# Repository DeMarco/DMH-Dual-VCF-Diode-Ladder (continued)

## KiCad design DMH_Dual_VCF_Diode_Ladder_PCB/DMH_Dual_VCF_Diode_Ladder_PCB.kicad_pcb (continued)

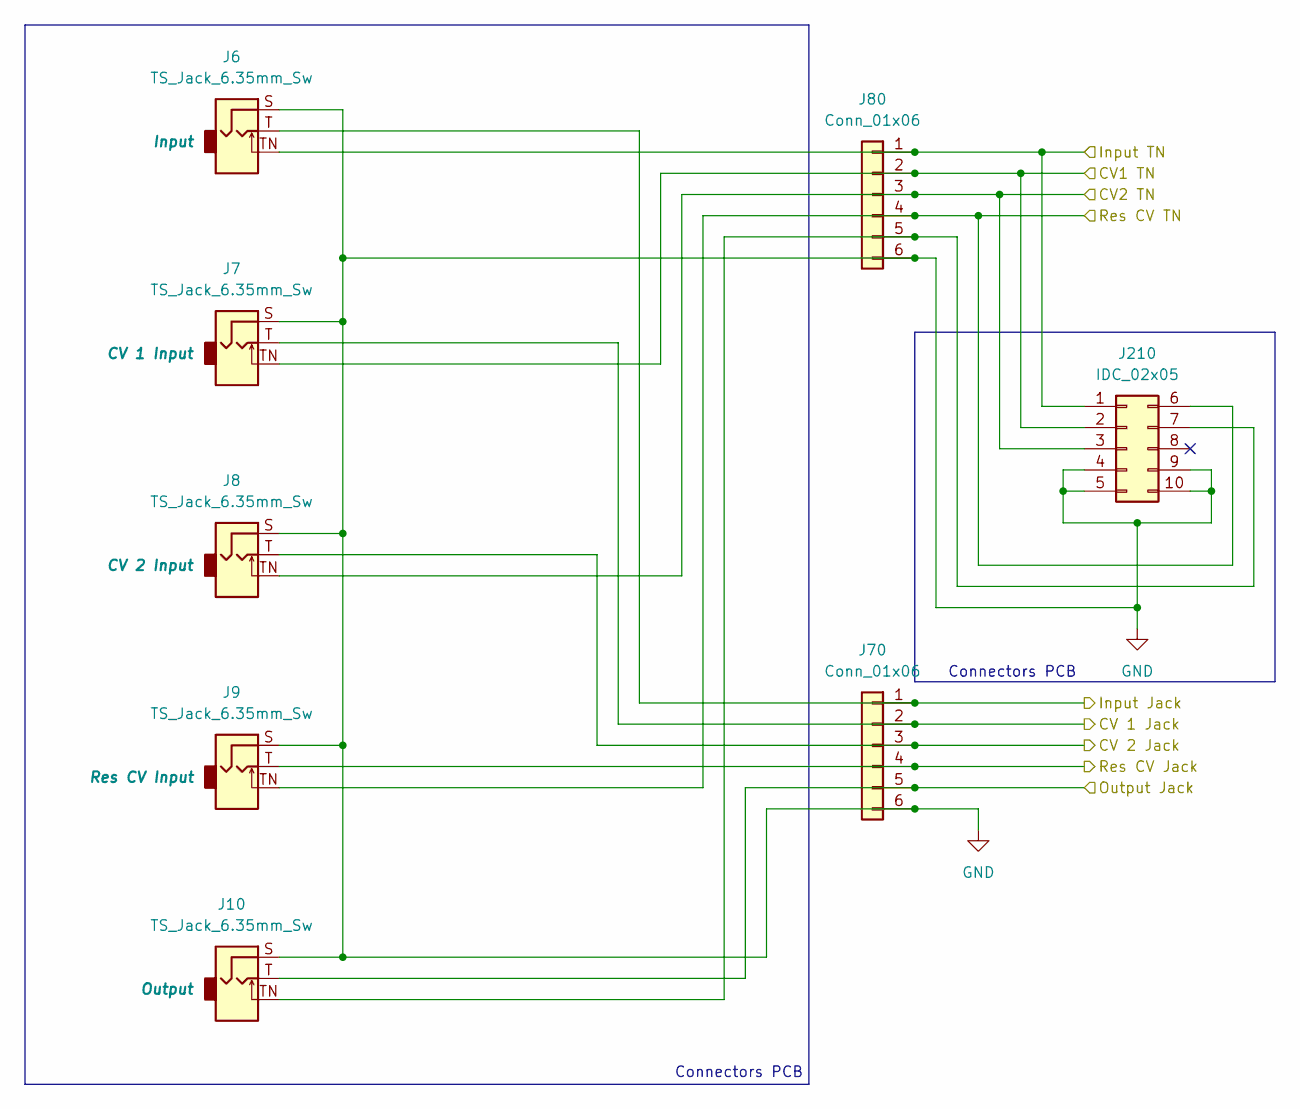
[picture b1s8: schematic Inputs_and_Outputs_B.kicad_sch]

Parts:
J6, J7, J8, J9, J10: TS_Jack_6.35mm_Sw; CUI_MJ-63052A
J70, J80: Conn_01x06; PinSocket_1x06_P2.54mm_Vertical
J210: IDC_02x05; IDC-Header_2x05_P2.54mm_Vertical_BackBone

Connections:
/CV Processing/CV1 A Input: J7.TN, J80.2, J210.2; also elsewhere on the board
/CV Processing/CV1 B Input: J7.T, J70.2; also elsewhere on the board
/CV Processing/CV2 A Input: J8.TN, J80.3, J210.3; also elsewhere on the board
/CV Processing/CV2 B Input: J8.T, J70.3; also elsewhere on the board
/Core Circuit B/Input: J6.T, J70.1; also elsewhere on the board
/Core Circuit B/Output: J10.T, J70.5; also elsewhere on the board
/Inputs and Outputs A/Feed Switch: J6.TN, J80.1, J210.1; also elsewhere on the board
/Inputs and Outputs A/Res CV Jack: J9.TN, J80.4, J210.6; also elsewhere on the board
/Inputs and Outputs B/Res CV Jack: J9.T, J70.4; also elsewhere on the board
GND: J6.S, J7.S, J8.S, J9.S, J10.S, J70.6, J80.6, J210.4, J210.5, J210.9, J210.10; also elsewhere on the board
unnamed: J10.TN, J80.5, J210.7

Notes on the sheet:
Connectors PCB

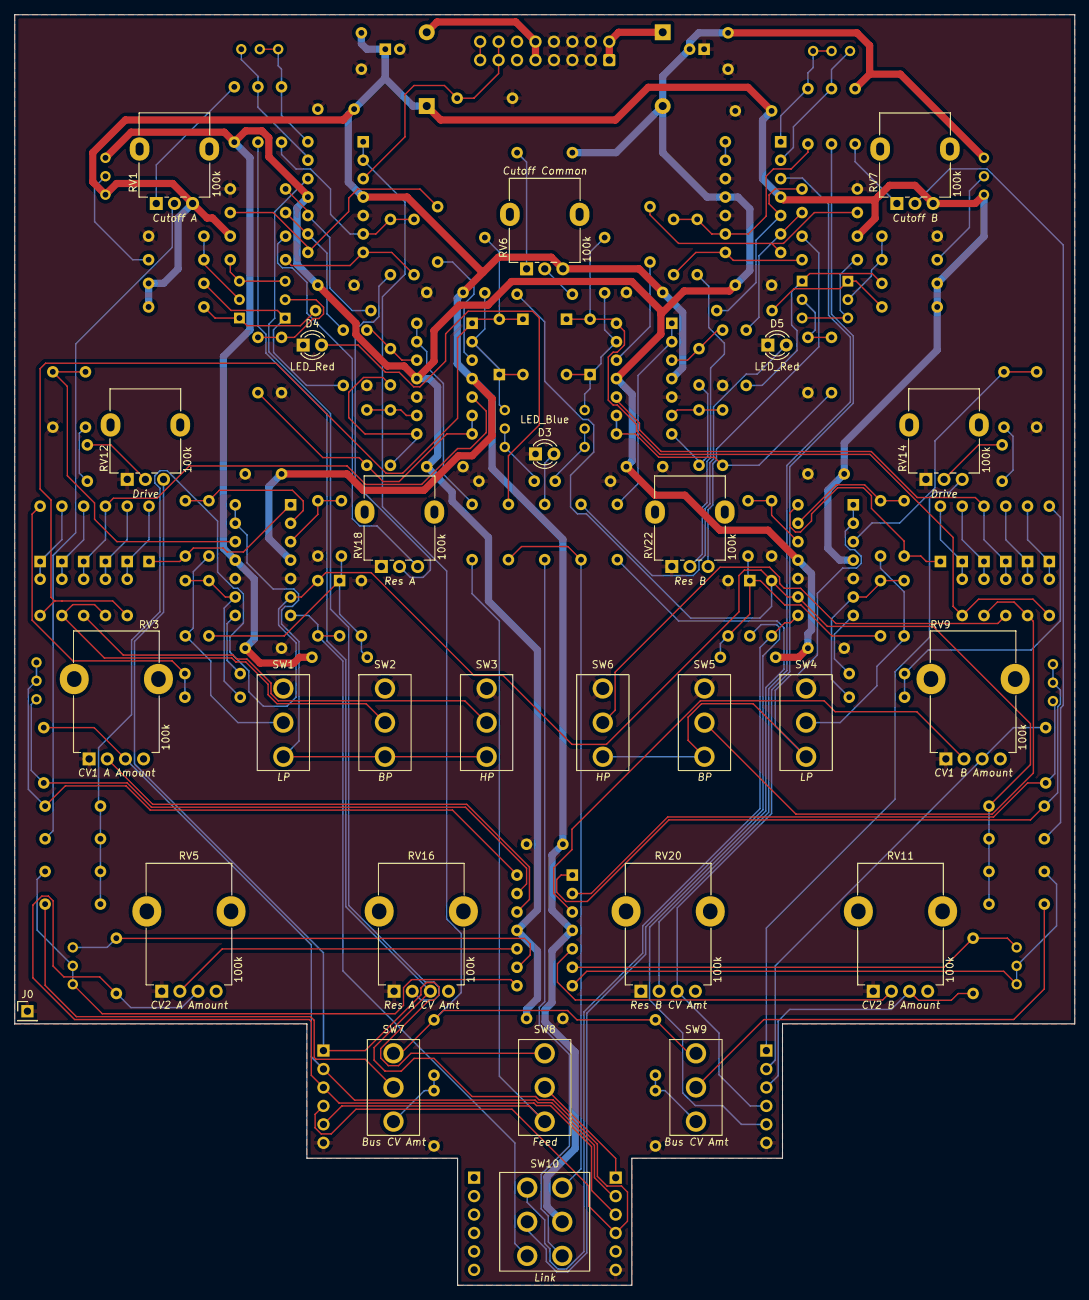
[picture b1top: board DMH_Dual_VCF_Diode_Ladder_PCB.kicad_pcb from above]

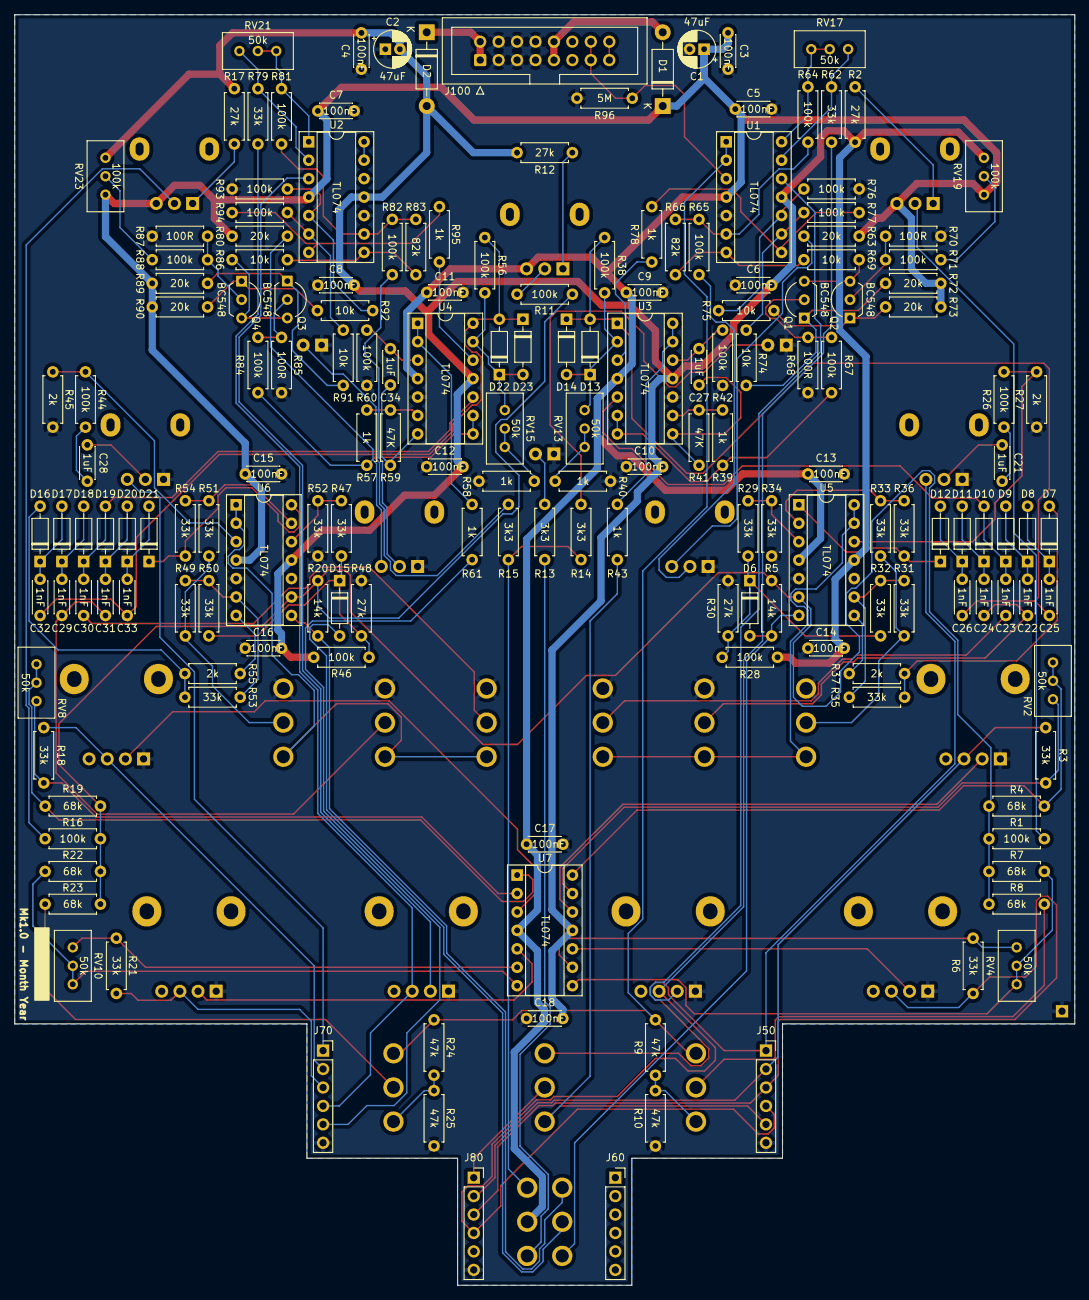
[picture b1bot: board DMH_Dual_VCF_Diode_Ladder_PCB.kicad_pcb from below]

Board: 2 copper layers, 146.0 x 175.0 mm, 201 parts (174 on the bottom side), 139 nets.

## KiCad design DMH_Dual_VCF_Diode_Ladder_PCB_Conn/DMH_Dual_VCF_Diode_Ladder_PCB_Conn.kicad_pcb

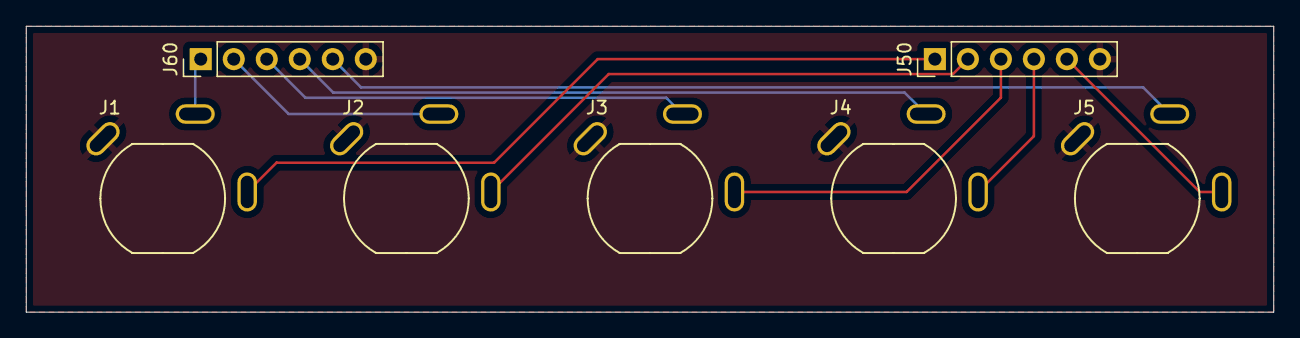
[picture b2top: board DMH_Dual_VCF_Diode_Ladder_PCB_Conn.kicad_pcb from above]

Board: 2 copper layers, 96.0 x 22.0 mm, 7 parts (0 on the bottom side), 11 nets.

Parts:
J1, J2, J3, J4, J5: TS_Jack_6.35mm_Sw; CUI_MJ-63052A
J50, J60: Conn_01x06; PinHeader_1x06_P2.54mm_Vertical

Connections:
/Core Circuit/(Bus) CV2 Input: J3.T, J50.3
/Core Circuit/CV1 Input: J2.T, J50.2
/Core Circuit/CV3 Input: J4.T, J50.4
/Core Circuit/Input: J1.T, J50.1
/Core Circuit/Output: J5.T, J50.5
GND: J1.S, J2.S, J3.S, J4.S, J5.S, J50.6, J60.6
unnamed: J1.TN, J60.1
unnamed: J2.TN, J60.2
unnamed: J3.TN, J60.3
unnamed: J4.TN, J60.4
unnamed: J5.TN, J60.5

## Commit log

2024-11-09 Copied Panel project from mono VCF repo
2024-11-09 Finished panel
2024-11-10 Changed line art
2024-11-18 Changed from unlink to split
2024-11-18 Added central cutoff knob
2024-11-21 Copied PCB and Connectors projects
2024-11-21 Changed features on panel
2024-11-24 Reorganized panel
    ... and added Feed switch.
2024-11-24 sync libs
2024-11-24 Started circuit schematic
2024-11-27 Updated attenuverter pot cutouts to P110KH1
2024-11-30 Starting Res CV design
2024-12-08 Generated BoM
2025-01-01 Concluded core and resonance circuits design
2025-01-01 Changed Bus CV switch silkscreen
2025-01-01 Schematic design in progress
2025-01-01 Added Bus CV buffering
2025-01-03 Made CV processing page
2025-01-03 Finished designing circuit
2025-01-03 Reannotated whole schematic
    OpAmp annotation is still tentative.
2025-01-03 Reannotated OpAmps and cleared errors
2025-01-03 Updated switches symbols and fps
2025-01-03 Placed panel hole references on Main PCB
2025-01-03 Placed location dependent components on PCB
2025-01-04 Placed ICs and prepared passives
2025-01-04 Re-annotated OpAmps as per PCB layout
2025-01-05 Component placement in progress
2025-01-07 Component placement done
2025-01-08 Corrections before routing in progress
2025-01-09 Routing ongoing
2025-01-09 Routing in progress
2025-01-10 Finished routing
